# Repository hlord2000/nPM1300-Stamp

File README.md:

# nPM1300 Module

## Overview

Compact module integrating Nordic Semiconductor's nPM1300 PMIC with all necessary passive components. Designed for easy integration into Bluetooth Low Energy embedded systems.

## Key Features

- 800 mA battery charger
- Dual 200 mA buck DCDC regulators
- Fuel gauge functionality
- System-level watchdog
- I2C control interface
- USB-C compatible

## Design Resources

- Schematic symbol available
- PCB footprint available

## Requirements for Design

- VSET1 and VSET2 resistors must be provided externally
- VDDIO must be provided externally, but could also be an output from one of your bucks or LDOs on the nPM1300
- If you use the LDOs, please include the recommended decoupling capacitors outside of the stamp.
- I2C pull-ups are required externally
- ESD protection must be provided externally

For detailed specifications, visit [Nordic Semiconductor's nPM1300 page](https://www.nordicsemi.com/Products/nPM1300).

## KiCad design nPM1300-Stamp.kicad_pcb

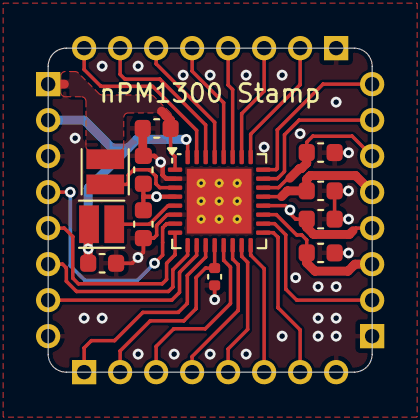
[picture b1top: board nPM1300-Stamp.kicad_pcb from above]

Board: 4 copper layers, 18.0 x 18.0 mm, 16 parts (0 on the bottom side), 30 nets.

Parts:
C1: 100nF; C_0402_1005Metric
C2, C3, C4, C7, C8: 10uF; C_0603_1608Metric
C5, C6: 1uF; C_0603_1608Metric
C13: 2.2uF; C_0603_1608Metric
J1, J2, J3, J4: Conn_01x08; nPM1300-PinHeader_1x08_P2.00mm_Vertical
L1, L2: 2.2uH; L_Cenker_CKCS201610
U1: nPM1300-QEXX; QFN-32-1EP_5x5mm_P0.5mm_EP3.6x3.6mm_ThermalVias

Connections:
/CC1: J3.7, U1.23 (CC1)
/CC2: J3.8, U1.24 (CC2)
/GPIO0: J1.4, U1.7 (GPIO0)
/GPIO1: J1.5, U1.8 (GPIO1)
/GPIO2: J1.6, U1.9 (GPIO2)
/GPIO3: J1.7, U1.10 (GPIO3)
/GPIO4: J2.1, U1.11 (GPIO4)
/LED0: J4.2, U1.25 (LED0)
/LED1: J4.3, U1.26 (LED1)
/LED2: J4.4, U1.27 (LED2)
/LS1_IN: J4.5, U1.28 (LSIN1/VINLDO1)
/LS1_OUT: J4.6, U1.29 (LSOUT1/VOUTLDO1)
/LS2_IN: J4.7, U1.30 (LSIN2/VINLDO2)
/LS2_OUT: J4.8, U1.31 (LSOUT2/VOUTLDO2)
/NTC: J3.2, U1.18 (NTC)
/SCL_NPM1300: J2.4, U1.14 (SCL)
/SDA_NPM1300: J2.3, U1.13 (SDA)
/SHPLD: J2.5, U1.15 (SHPHLD)
/VBAT: C13.1, J3.3, U1.19 (VBAT)
/VBUS_IN: C5.1, J3.5, U1.21 (VBUS)
/VBUS_OUT: C6.1, J3.6, U1.22 (VBUSOUT)
/VDDIO: C1.1, J2.2, U1.12 (VDDIO)
/VOUT1: C7.1, J1.1, L1.1, U1.1 (VOUT1)
/VOUT2: C8.1, J1.2, L2.1, U1.32 (VOUT2)
/VSET1: J2.7, U1.17 (VSET1)
/VSET2: J2.6, U1.16 (VSET2)
/VSYS: C2.1, C3.1, C4.1, J3.4, U1.4 (PVDD), U1.20 (VSYS)
GND: C1.2, C2.2, C3.2, C4.2, C5.2, C6.2, C7.2, C8.2, C13.2, J1.3, J1.8, J2.8, J3.1, J4.1, U1.2 (PVSS1), U1.6 (PVSS2), U1.33 (AVSS)
unnamed: L1.2, U1.3 (SW1)
unnamed: L2.2, U1.5 (SW2)

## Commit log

2024-09-30 Created README and added image
2024-09-30 Added nPM1300 library
2024-09-30 Added JLCPCB production files
2024-10-01 Updated README with external requirements
2024-10-02 Updated layout to use thicker traces for power delivery
2024-10-02 Updated LCSC part number for 2.2uF cap
